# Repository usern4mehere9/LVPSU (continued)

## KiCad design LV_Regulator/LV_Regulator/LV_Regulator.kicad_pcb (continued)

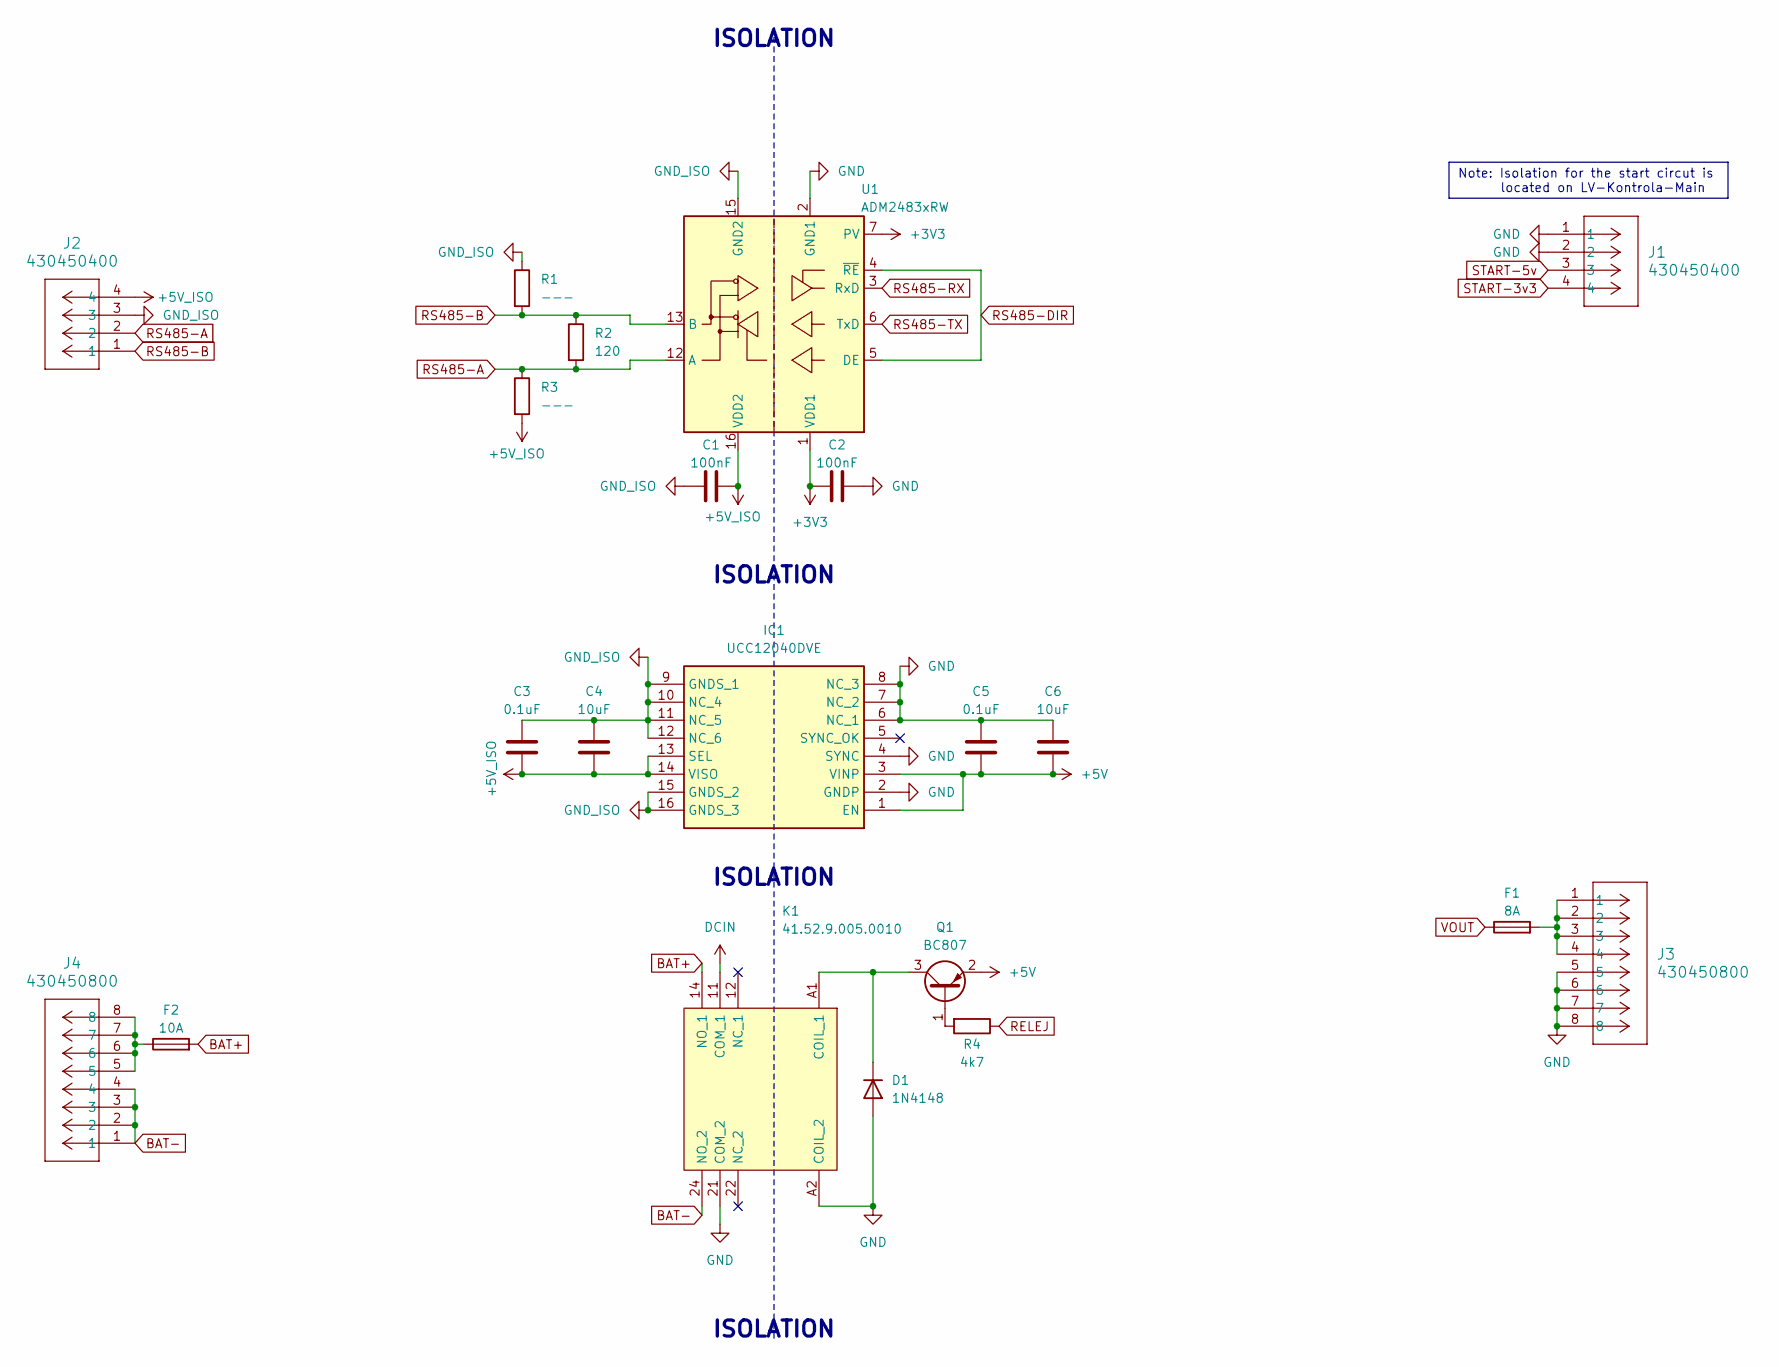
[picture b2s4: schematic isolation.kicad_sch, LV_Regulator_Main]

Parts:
C1, C2: 100nF; C_1206_3216Metric_Pad1.33x1.80mm_HandSolder
C3, C5: 0.1uF; C_1206_3216Metric_Pad1.33x1.80mm_HandSolder
C4, C6: 10uF; C_1206_3216Metric_Pad1.33x1.80mm_HandSolder
D1: 1N4148; D_1206_3216Metric_Pad1.42x1.75mm_HandSolder
F1: 8A; Fuse_1206_3216Metric_Pad1.42x1.75mm_HandSolder
F2: 10A; Fuse_1206_3216Metric_Pad1.42x1.75mm_HandSolder
IC1: UCC12040DVE; SOIC127P1030X265-16N; Mouser Part Number 595-UCC12040DVE
J1, J2: 430450400; CONN_SD-43045-001_04_MOL
J3, J4: 430450800; CONN_SD-43045-001_08_MOL
K1: 41.52.9.005.0010; 415290050010; Manufacturer_Part_Number 41.52.9.005.0010
Q1: BC807; SOT-23W_Handsoldering
R1, R3: ---; R_1206_3216Metric_Pad1.30x1.75mm_HandSolder
R2: 120; R_1206_3216Metric_Pad1.30x1.75mm_HandSolder
R4: 4k7; R_1206_3216Metric_Pad1.30x1.75mm_HandSolder
U1: ADM2483xRW; SOIC-16W_7.5x10.3mm_P1.27mm

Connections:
3V3_EXT: J1.4; also elsewhere on the board
5V_EXT: J1.3; also elsewhere on the board
+5V: C5.1, C6.1, IC1.1 (EN), IC1.3 (VINP), Q1.2 (E); also elsewhere on the board
+5V_ISO: C1.2, C3.1, C4.1, IC1.13 (SEL), IC1.14 (VISO), J2.4, R3.2, U1.16 (VDD2)
BAT+: F2.2, K1.14 (NO_1); also elsewhere on the board
BAT-: J4.1, J4.2, J4.3, J4.4, K1.24 (NO_2); also elsewhere on the board
GND: C2.2, C5.2, C6.2, D1.2 (A), IC1.2 (GNDP), IC1.4 (SYNC), IC1.6 (NC_1), IC1.7 (NC_2), IC1.8 (NC_3), J1.1, J1.2, J3.5, J3.6, J3.7, J3.8, K1.21 (COM_2), K1.A2 (COIL_2), U1.2 (GND1), U1.8 (GND1); also elsewhere on the board
GND_ISO: C1.1, C3.2, C4.2, IC1.9 (GNDS_1), IC1.10 (NC_4), IC1.11 (NC_5), IC1.12 (NC_6), IC1.15 (GNDS_2), IC1.16 (GNDS_3), J2.3, R1.1, U1.9 (GND2), U1.15 (GND2); also elsewhere on the board
unnamed: D1.1 (K), K1.A1 (COIL_1), Q1.3 (C)
unnamed: F1.2, J3.1, J3.2, J3.3, J3.4
unnamed: F2.1, J4.5, J4.6, J4.7, J4.8
unnamed: Q1.1 (B), R4.2
RELEJ: R4.1; also elsewhere on the board
RS485-A: J2.2, R2.2, R3.1, U1.12 (A)
RS485-B: J2.1, R1.2, R2.1, U1.13 (B)
RS485-DIR: U1.4 (~RE), U1.5 (DE); also elsewhere on the board
RS485-RX: U1.3 (RxD); also elsewhere on the board
RS485-TX: U1.6 (TxD); also elsewhere on the board
SYS: K1.11 (COM_1); also elsewhere on the board
VBAT: C2.1, U1.1 (VDD1), U1.7 (PV); also elsewhere on the board
VOUT: F1.1; also elsewhere on the board

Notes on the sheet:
ISOLATION
Note: Isolation for the start circut is located on LV-Kontrola-Main

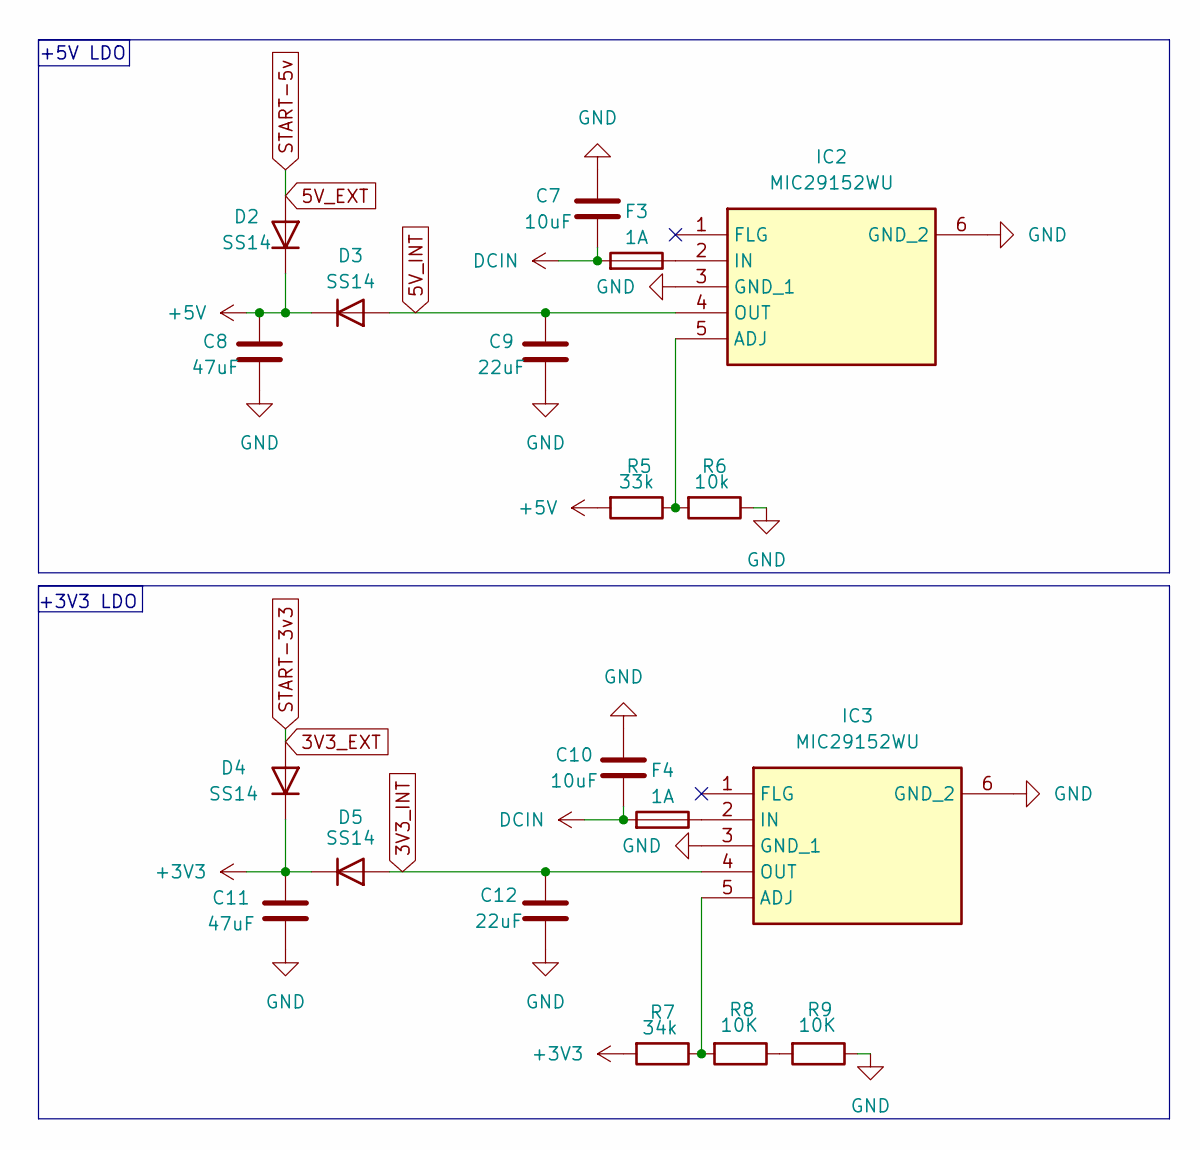
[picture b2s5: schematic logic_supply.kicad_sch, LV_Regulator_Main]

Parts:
C7, C10: 10uF; C_1206_3216Metric_Pad1.33x1.80mm_HandSolder
C8, C11: 47uF; C_1206_3216Metric_Pad1.33x1.80mm_HandSolder
C9, C12: 22uF; C_1206_3216Metric_Pad1.33x1.80mm_HandSolder
D2, D3, D4, D5: SS14; CR_SMA_403AE_OSI
F3, F4: 1A; Fuse_1206_3216Metric_Pad1.42x1.75mm_HandSolder
IC2, IC3: MIC29152WU; Mouser Part Number 998-MIC29152WU
R5: 33k; R_1206_3216Metric_Pad1.30x1.75mm_HandSolder
R6: 10k; R_1206_3216Metric_Pad1.30x1.75mm_HandSolder
R7: 34k; R_1206_3216Metric_Pad1.30x1.75mm_HandSolder
R8, R9: 10K; R_1206_3216Metric_Pad1.30x1.75mm_HandSolder

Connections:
3V3_EXT: D4.2 (A); also elsewhere on the board
3V3_INT: C12.2, D5.2 (A), IC3.4 (OUT); also elsewhere on the board
5V_EXT: D2.2 (A); also elsewhere on the board
5V_INT: C9.2, D3.2 (A), IC2.4 (OUT); also elsewhere on the board
+5V: C8.2, D2.1 (K), D3.1 (K), R5.2; also elsewhere on the board
GND: C7.1, C8.1, C9.1, C10.1, C11.1, C12.1, IC2.3 (GND_1), IC2.6 (GND_2), IC3.3 (GND_1), IC3.6 (GND_2), R6.1, R9.1; also elsewhere on the board
unnamed: IC2.5 (ADJ), R5.1, R6.2
unnamed: F3.1, IC2.2 (IN)
unnamed: IC3.5 (ADJ), R7.1, R8.2
unnamed: F4.1, IC3.2 (IN)
unnamed: R8.1, R9.2
SYS: C7.2, C10.2, F3.2, F4.2; also elsewhere on the board
VBAT: C11.2, D4.1 (K), D5.1 (K), R7.2; also elsewhere on the board

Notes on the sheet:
+5V LDO
+3V3 LDO

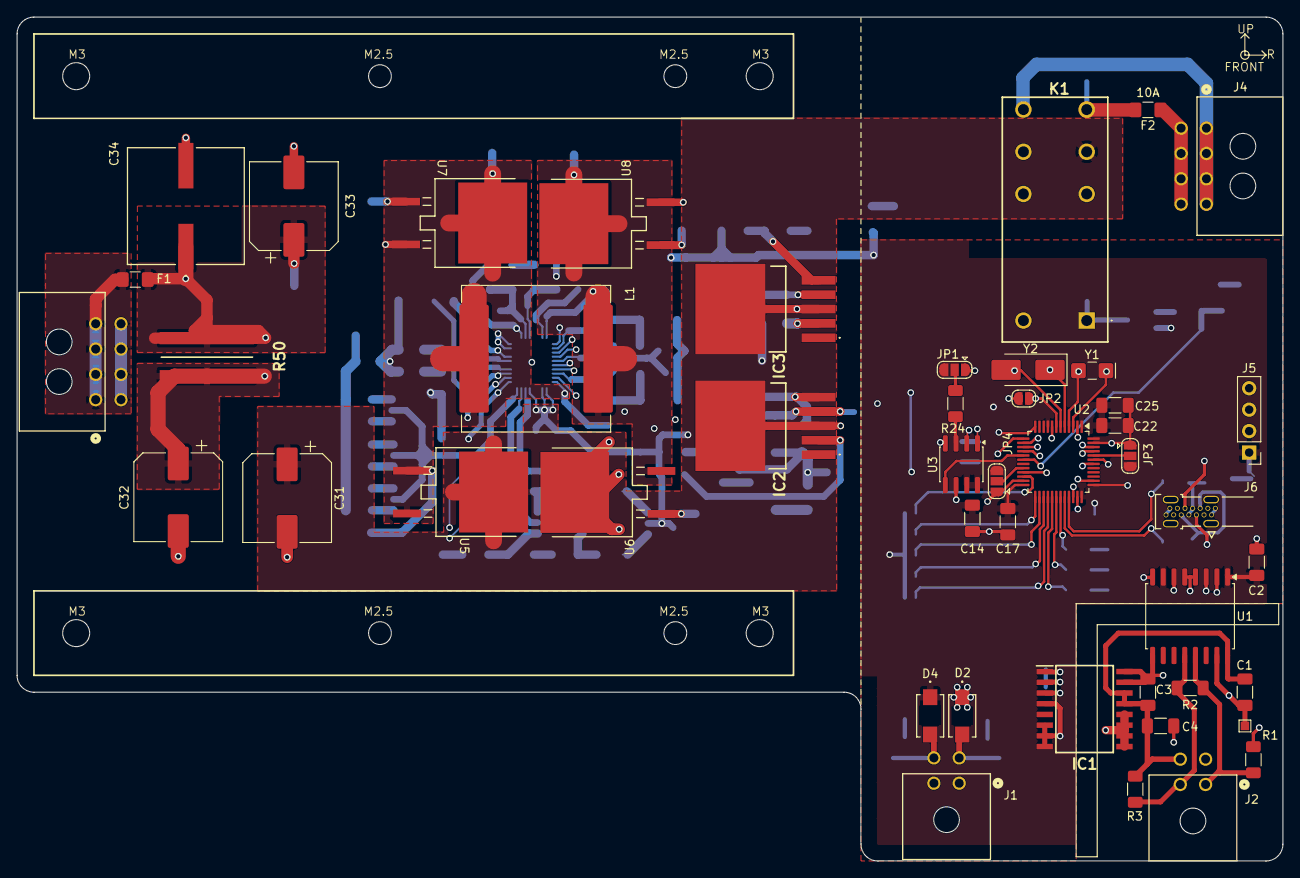
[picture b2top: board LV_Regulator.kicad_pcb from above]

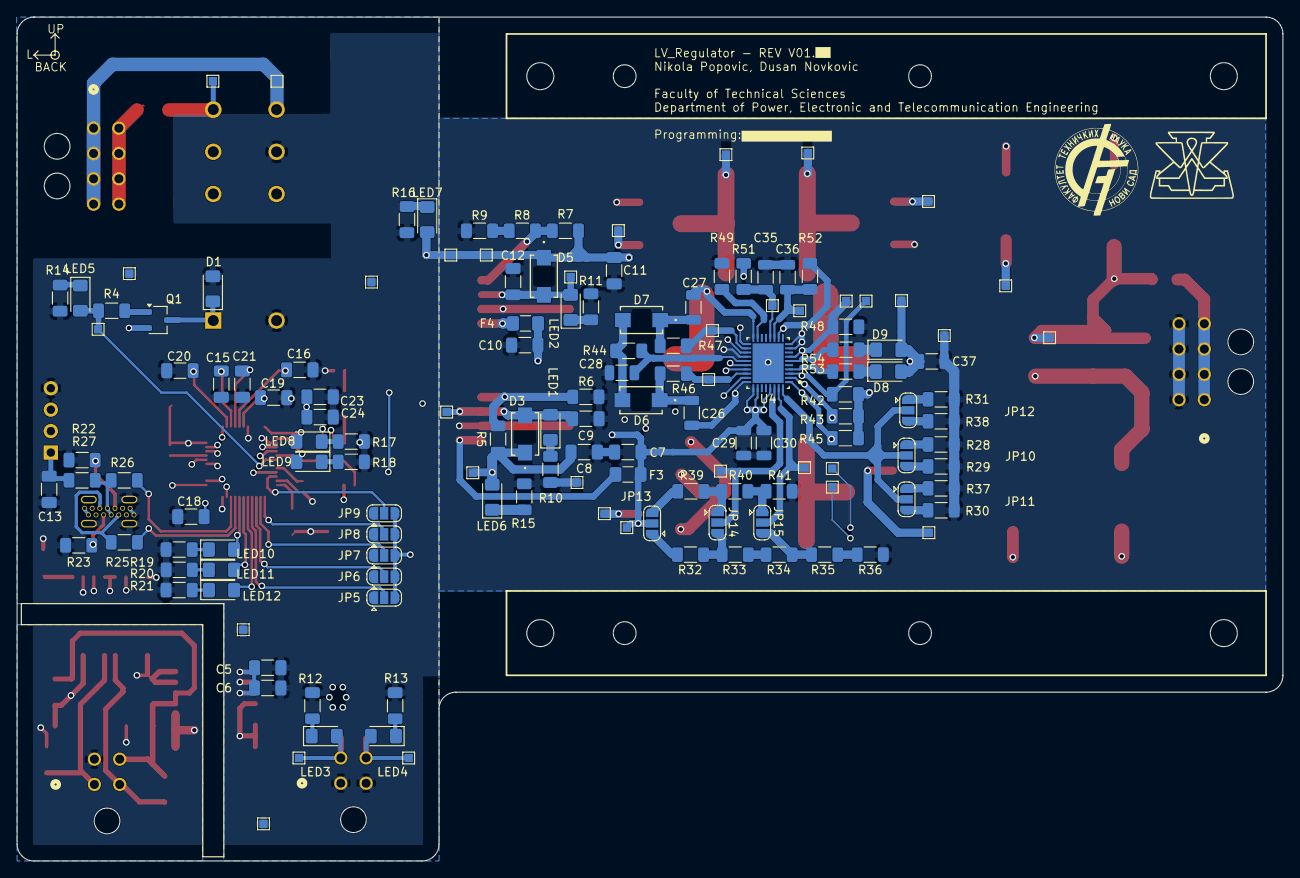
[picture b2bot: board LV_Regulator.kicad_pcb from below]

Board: 4 copper layers, 150.0 x 100.0 mm, 190 parts (144 on the bottom side), 113 nets.

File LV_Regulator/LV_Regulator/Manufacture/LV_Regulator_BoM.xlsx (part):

Id | Designator | Footprint | Quantity | Designation | Supplier and ref
1 | 3V3 | LED_1206_3216Metric_Pad1.42x1.75mm_HandSolder | 1 | 3V3 (YELLOW) | https://www.digikey.com/en/products/detail/kingbright/APT321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 | https://eu.mouser.com/ProductDetail/Bivar/SM1206UYC?qs=jaLxT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
2 | 3V3_EXT | LED_1206_3216Metric_Pad1.42x1.75mm_HandSolder | 1 | 3V3_EXT (YELLOW) | https://www.digikey.com/en/products/detail/kingbright/APT321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 | https://eu.mouser.com/ProductDetail/Bivar/SM1206UYC?qs=jaLxT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
3 | 3V3_INT | LED_1206_3216Metric_Pad1.42x1.75mm_HandSolder | 1 | 3V3_INT (YELLOW) | https://www.digikey.com/en/products/detail/kingbright/APT321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 | https://eu.mouser.com/ProductDetail/Bivar/SM1206UYC?qs=jaLxT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
4 | 5V | LED_1206_3216Metric_Pad1.42x1.75mm_HandSolder | 1 | 5V (RED) | https://www.digikey.com/en/products/detail/kingbright/APT321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 | https://eu.mouser.com/ProductDetail/Bivar/SM1206URC?qs=jaLxT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
5 | 5V_EXT | LED_1206_3216Metric_Pad1.42x1.75mm_HandSolder | 1 | 5V_EXT (RED) | https://www.digikey.com/en/products/detail/kingbright/APT321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 | https://eu.mouser.com/ProductDetail/Bivar/SM1206URC?qs=jaLxT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
6 | 5V_INT | LED_1206_3216Metric_Pad1.42x1.75mm_HandSolder | 1 | 5V_INT (RED) | https://www.digikey.com/en/products/detail/kingbright/APT321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 | https://eu.mouser.com/ProductDetail/Bivar/SM1206URC?qs=jaLxT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
7 | C1, C2, C13, C14, C17, C18, C22, C24, C25 | C_1206_3216Metric_Pad1.33x1.80mm_HandSolder | 9 | 100nF | https://www.digikey.com/en/products/detail/kemet/c1206y104k9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 | https://eu.mouser.com/ProductDetail/KEMET/C1206Y104K9RACTU?q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
8 | C3, C5, C19 | C_1206_3216Metric_Pad1.33x1.80mm_HandSolder | 3 | 0.1uF | https://www.digikey.com/en/products/detail/kemet/c1206y104k9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 | https://eu.mouser.com/ProductDetail/KEMET/C1206Y104K9RACTU?q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
9 | C4, C6, C7, C10, C23 | C_1206_3216Metric_Pad1.33x1.80mm_HandSolder | 5 | 10uF | https://www.digikey.com/en/products/detail/samsung-electro-m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 | https://eu.mouser.com/ProductDetail/Samsung-Electro-Mechanic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
10 | C8, C11 | C_1206_3216Metric_Pad1.33x1.80mm_HandSolder | 2 | 47uF | https://www.digikey.com/en/products/detail/taiyo-yuden/MLASJ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 | https://eu.mouser.com/ProductDetail/TAIYO-YUDEN/MLASJ319LB54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
11 | C9, C12 | C_1206_3216Metric_Pad1.33x1.80mm_HandSolder | 2 | 22uF | https://www.digikey.com/en/products/detail/murata-electronic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 | https://eu.mouser.com/ProductDetail/Murata-Electronics/GGM31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
12 | C15, C20 | C_1206_3216Metric_Pad1.33x1.80mm_HandSolder | 2 | 8pF | https://www.digikey.com/en/products/detail/walsin-technology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 | https://eu.mouser.com/ProductDetail/Walsin/1206N8R0B500CT?qs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
13 | C16, C21 | C_1206_3216Metric_Pad1.33x1.80mm_HandSolder | 2 | 12pF | https://www.digikey.com/en/products/detail/kyocera-avx/KGM31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 | https://eu.mouser.com/ProductDetail/KYOCERA-AVX/12065A120KAT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
14 | C26, C27, C35, C36 | C_1206_3216Metric | 4 | 100nF | https://www.digikey.com/en/products/detail/kemet/c1206y104k9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 | https://eu.mouser.com/ProductDetail/KEMET/C1206Y104K9RACTU?q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
15 | C28, C37 | C_1206_3216Metric | 2 | 4.7uF | https://www.digikey.com/en/products/detail/walsin-technology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 | https://eu.mouser.com/ProductDetail/Walsin/SH31B475K250CT?qs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
16 | C29, C30 | C_1206_3216Metric | 2 | 1uF | https://www.digikey.com/en/products/detail/kemet/c1206c105k1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 | https://eu.mouser.com/ProductDetail/KEMET/C1206C105K1RAC7210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
17 | C31 | CAP_UCD_12P5X13P5_NCH | 1 | 56uF | https://www.digikey.com/en/products/detail/eaton-electronics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 | https://eu.mouser.com/ProductDetail/Eaton-Electronics/EHBSA0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
18 | C32, C33 | CP_Elec_10x10 | 2 | 47uF | https://www.digikey.com/en/products/detail/vishay-beyschlag-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 | https://eu.mouser.com/ProductDetail/Vishay-BC-Components/MAL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
19 | C34 | CAP_UCD_12P5X13P5_NCH | 1 | 180uF | https://www.digikey.com/en/products/detail/nichicon/ucz1j181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 | https://eu.mouser.com/ProductDetail/Nichicon/UCZ1J181MNS1MS?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
20 | COM, START | CONN_SD-43045-001_04_MOL | 2 | 430450400 | https://www.digikey.com/en/products/detail/molex/0430450400/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 | https://eu.mouser.com/ProductDetail/Molex/43045-0400?qs=UeCe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
21 | D1 | D_1206_3216Metric_Pad1.42x1.75mm_HandSolder | 1 | 1N4148 | https://www.digikey.com/en/products/detail/taiwan-semiconduc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 | https://eu.mouser.com/ProductDetail/Taiwan-Semiconductor/1N4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
22 | D2, D3, D4, D5, D6, D7 | CR_SMA_403AE_OSI | 6 | SS14 | https://www.digikey.com/en/products/detail/onsemi/SS14/965474 | https://eu.mouser.com/ProductDetail/onsemi/SS14?qs=mVVXn4M53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
23 | D8, D9 | D_1206_3216Metric_Pad1.42x1.75mm_HandSolder | 2 | LED(YELLOW) | https://www.digikey.com/en/products/detail/kingbright/APT321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 | https://eu.mouser.com/ProductDetail/Bivar/SM1206UYC?qs=jaLxT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
24 | DIAG | MOLEX_2169890001 | 1 | 2169890001 | https://www.digikey.com/en/products/detail/wec/216989-0001/29353332 | https://eu.mouser.com/ProductDetail/Molex/216989-0001?qs=DRk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
25 | ERR | LED_1206_3216Metric_Pad1.42x1.75mm_HandSolder | 1 | ERR(RED) | https://www.digikey.com/en/products/detail/kingbright/APT321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 | https://eu.mouser.com/ProductDetail/Bivar/SM1206URC?qs=jaLxT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
26 | F1 | Fuse_1206_3216Metric_Pad1.42x1.75mm_HandSolder | 1 | 8A | https://www.digikey.com/en/products/detail/bel-fuse-inc/C1F-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 | https://eu.mouser.com/ProductDetail/Bel-Fuse/C1F-8?qs=Mr%252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
27 | F2 | Fuse_1206_3216Metric_Pad1.42x1.75mm_HandSolder | 1 | 10A | https://www.digikey.com/en/products/detail/bel-fuse-inc/0685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 | https://eu.mouser.com/ProductDetail/Bel-Fuse/0685P9100-01?qs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
28 | F3, F4 | Fuse_1206_3216Metric_Pad1.42x1.75mm_HandSolder | 2 | 1A | https://www.digikey.com/en/products/detail/bel-fuse-inc/C1F-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 | https://eu.mouser.com/ProductDetail/Bel-Fuse/C1F-1?qs=Mr%252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
29 | IC1 | SOIC127P1030X265-16N | 1 | UCC12040DVE | https://www.digikey.com/en/products/detail/texas-instruments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 | https://eu.mouser.com/ProductDetail/Texas-Instruments/UCC120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
30 | IC2, IC3 | MIC29152WU | 2 | MIC29152WU | https://www.digikey.com/en/products/detail/microchip-technol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 | https://eu.mouser.com/ProductDetail/Microchip-Technology/MIC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
31 | J3, PWR_IN | CONN_SD-43045-001_08_MOL | 2 | 430450800 | https://www.digikey.com/en/products/detail/molex/0430450800/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 | https://eu.mouser.com/ProductDetail/Molex/43045-0800?qs=MGlP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
32 | K1 | LED_1206_3216Metric_Pad1.42x1.75mm_HandSolder | 1 | REL(GREEN) | https://www.digikey.com/en/products/detail/kingbright/APT321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 | https://eu.mouser.com/ProductDetail/Bivar/SM1206GC?qs=jaLxTF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
33 | K1 | 415000000000 | 1 | 41.52.9.005.0010 | https://elektroleum.rs/proizvod/finder-41-52-9-005-0010-pcb-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 | //
34 | L1 | L_APV_APH1770 | 1 | 10uH | https://www.digikey.com/en/products/detail/bourns-inc/srp177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 | https://eu.mouser.com/ProductDetail/Bourns/SRP1770TA-100M?qs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
35 | OK | LED_1206_3216Metric_Pad1.42x1.75mm_HandSolder | 1 | OK (GREEN) | https://www.digikey.com/en/products/detail/kingbright/APT321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 | https://eu.mouser.com/ProductDetail/Bivar/SM1206GC?qs=jaLxTF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
36 | Q1 | SOT-23W_Handsoldering | 1 | BC807 | https://www.digikey.com/en/products/detail/onsemi/BC807-25LT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 | https://eu.mouser.com/ProductDetail/Rectron/BC807?qs=7pEAo90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
37 | R1, R3, R42, R43, R44, R45, R46, R47, R48 | R_1206_3216Metric_Pad1.30x1.75mm_HandSolder | 9 | --- | https://www.digikey.com/en/products/detail/yageo/rc1206jr-07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 | https://eu.mouser.com/ProductDetail/YAGEO/RC1206JR-070RL?qs=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
38 | R2 | R_1206_3216Metric_Pad1.30x1.75mm_HandSolder | 1 | 120 | https://www.digikey.com/en/products/detail/yageo/ar1206jr-07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 | https://eu.mouser.com/ProductDetail/YAGEO/RC1206JR-070RL?qs=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
39 | R4 | R_1206_3216Metric_Pad1.30x1.75mm_HandSolder | 1 | 4k7 | https://www.digikey.com/en/products/detail/yageo/re1206dre07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 | https://eu.mouser.com/ProductDetail/YAGEO/RE1206DRE074K7L?qs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
40 | R5 | R_1206_3216Metric_Pad1.30x1.75mm_HandSolder | 1 | 33k | https://www.digikey.com/en/products/detail/yageo/rt1206brd07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 | https://eu.mouser.com/ProductDetail/YAGEO/RT1206BRD0733KL?qs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
41 | R6, R53, R54 | R_1206_3216Metric_Pad1.30x1.75mm_HandSolder | 3 | 10k | https://www.digikey.com/en/products/detail/rohm-semiconducto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 | https://eu.mouser.com/ProductDetail/ROHM-Semiconductor/SFR18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

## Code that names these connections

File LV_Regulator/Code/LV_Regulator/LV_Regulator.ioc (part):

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Mcu.Name=STM32F103C(8-B)Tx
Mcu.Package=LQFP48
Mcu.UserName=STM32F103C8Tx
PA0-WKUP.Signal=ADCx_IN0
PA1.Signal=ADCx_IN1
PA10.GPIOParameters=GPIO_Label
PA10.GPIO_Label=DIAG_RX
PA10.Signal=GPIO_Output
PA11.Mode=Device
PA11.Signal=USB_DM
PA12.Mode=Device
PA12.Signal=USB_DP
PA13.Mode=Serial_Wire
PA13.Signal=SYS_JTMS-SWDIO
PA14.Mode=Serial_Wire
PA14.Signal=SYS_JTCK-SWCLK
PA15.GPIOParameters=GPIO_Label
PA15.GPIO_Label=CE_N
PA15.Signal=GPIO_Output
PA2.GPIOParameters=GPIO_Label
PA2.GPIO_Label=DIAG_OK
PA2.Signal=GPIO_Output
PA3.GPIOParameters=GPIO_Label
PA3.GPIO_Label=DIAG_ERR
PA3.Signal=GPIO_Output
PA4.Mode=NSS_Signal_Hard_Output
PA4.Signal=SPI1_NSS
PA5.Mode=Full_Duplex_Master
PA5.Signal=SPI1_SCK
PA6.Mode=Full_Duplex_Master
PA6.Signal=SPI1_MISO
PA7.Mode=Full_Duplex_Master
PA7.Signal=SPI1_MOSI
PA8.GPIOParameters=GPIO_Label
PA8.GPIO_Label=DIAG_RUN
PA8.Signal=GPIO_Output
PA9.GPIOParameters=GPIO_Label
PA9.GPIO_Label=DIAG_TX
PA9.Signal=GPIO_Output
PB0.GPIOParameters=GPIO_Label
PB0.GPIO_Label=RELEJ
PB0.Signal=GPIO_Output
PB10.GPIOParameters=GPIO_Label
PB10.GPIO_Label=INT_N
PB10.Signal=GPIO_Input
PB11.GPIOParameters=GPIO_Label
PB11.GPIO_Label=ADR1
PB11.Signal=GPIO_Output
PB12.GPIOParameters=GPIO_Label
PB12.GPIO_Label=ADR2
PB12.Signal=GPIO_Output
PB13.GPIOParameters=GPIO_Label
PB13.GPIO_Label=ADR3
PB13.Signal=GPIO_Output
PB14.GPIOParameters=GPIO_Label
PB14.GPIO_Label=ADR4
PB14.Signal=GPIO_Output
PB15.GPIOParameters=GPIO_Label
PB15.GPIO_Label=ADR5
PB15.Signal=GPIO_Output
PB2.GPIOParameters=GPIO_Label
PB2.GPIO_Label=BOOT1
PB2.Signal=GPIO_Input
PB6.Mode=Asynchronous
PB6.Signal=USART1_TX
PB7.Mode=Asynchronous
PB7.Signal=USART1_RX
PB8.Mode=I2C
PB8.Signal=I2C1_SCL
PB9.Mode=I2C
PB9.Signal=I2C1_SDA
PC13-TAMPER-RTC.GPIOParameters=GPIO_Label
PC13-TAMPER-RTC.GPIO_Label=USART1_DIR
PC13-TAMPER-RTC.Signal=GPIO_Output
PC14-OSC32_IN.Mode=LSE-External-Oscillator
PC14-OSC32_IN.Signal=RCC_OSC32_IN
PC15-OSC32_OUT.Mode=LSE-External-Oscillator
PC15-OSC32_OUT.Signal=RCC_OSC32_OUT
PD0-OSC_IN.Mode=HSE-External-Oscillator
PD0-OSC_IN.Signal=RCC_OSC_IN
PD1-OSC_OUT.Mode=HSE-External-Oscillator
PD1-OSC_OUT.Signal=RCC_OSC_OUT
RCC.SYSCLKFreq_VALUE=72000000
RCC.SYSCLKSource=RCC_SYSCLKSOURCE_PLLCLK
board=custom

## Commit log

2026-01-19 Initial commit
    Blank KiCad files for later use
2026-01-19 Folder structure added
    Added a folder structure for documentation, code and component data; Added basic info to KiCad files
2026-01-20 Added components
    Added some basic isolation components to the LV_Regulator schematic.
2026-01-20 Modified LV_Regulator schematic; Added basic code configuration for LV_Reulator
    Added the MCU to the schematic and some basic passives around it;
    Added the basic STM32 program structure and set up the pin configuration to reflect the schematic.
2026-01-26 Created initial STM projects
    Created basic blank project and added some pin definitions
2026-01-31 Added LDOs
    Added the two LDOs for 3v3 and 5v logic supply.
2026-02-03 Kicad Schematic Progress
    Put down basic components and imported TI FET's & Buck-Boost Controller, as well as some of the basic connections between Controller and FET's.
2026-02-03 Added a lot
    Created a schematic hierarchy for LV_Regulator, added connectors, added start logic, added address select jumpers for RS485, implemented start isolation on LV_Kontrola_Main,...
2026-02-03 Kicad Regulator & Buck Boost controller Schematic Progress
    Put down basic components and imported TI FET's & Buck-Boost Controller, as well as some of the basic connections between Controller and FET's.
2026-02-05 Fixed last commit
    Fixed all mistakes from the last push
2026-02-05 Added Start Control
    Added Start Control MCU to the LV_Kontrola_Main, added hsc/lsc to LV_Regulator, fixed component numbering
2026-02-09 Added Stat logic
    Added start mcu and associated components to the LV_Kontrola_Main schematic, added STM32CubeIDE project and basic configuration, added fuses to LV_Regulator
2026-02-10 Continuation of BQ25858 Schematic drawing
    Added more components from the examples schematic provided from TI.
2026-03-03 LV_Regulator Control changes
    Added debug and development equipment, added config. eeprom, more...
2026-03-11 Update & Further Progress on Regulator Controller Schematic
    Nikola Popovic added Frequency choice jumpers
    I added Jumpers for Voltage trigger selection
    Made global Labels for MCU pin connection, connected PG & STAT Diodes as well as connected ACN & ACP pins.
2026-03-11 Update Schematic, moved MOSFETS box
2026-03-11 Updated Note for Regulator
2026-03-12 Regulator Update & MCU pins
    Update schematic and connected Regulator to MCU
2026-03-16 added certain footprints
    Added footprints for certain parts such as the BQ25858Q1 regulator controller & CSD19506 MOSFET for PCB design and put in footprints (will need change)
2026-03-17 Various changes
2026-03-17 Multiple Footprints Added
2026-03-18 Changes of PCB and Schematic files for the LV_Regulator
    Removed old LDOs, added new LDOs, defined initial pcb size and I/O ports
2026-03-20 Update to LV_Regulator schematic
    Chosen some component's footprints as well as made a page for test points, etc.
2026-03-20 Multiple Updates
    Added footprints and purchase links to the MCU page and updated some footprints on the Regulator Page from smd to SMD Handsolder
2026-03-20 Added footprints and Test points
    Added test points, yet to connect them have to find where they all go exactly
2026-03-27 Added Footprints & Links for Component Purchase
2026-03-28 PCB Layout definitions part 2
    Added isolation keepouts
2026-03-28 Halfway Push of adding 3D models to PCB layout components
    Pushing with components left to add to finish on main PC
2026-03-29 Added 3D models to components part 2
    Modeled some Custom .step models for components whose 3D models I couldn't find, and imported the rest.
2026-03-31 Initial Routing for tje LV_Regulator control portion
    Changes to the schematic were made for simpler routing
2026-04-03 LV Regulator Switching layout Started
    Rough placement of components bigger components, a well as giving a capacitor a 3D model it lacked for the 3D View.
    More precise placement is in queue and actual PCB routing.
2026-04-04 Component Placement and Routing
2026-04-07 Continued PCB Routing
2026-04-07 PCB routing and TP placement
    Finished first PCB routing and started TP placement
2026-04-07 Changes to LV_Kontrola_Main
    Added a lot to the schematic, fixed component libs, mics...
2026-04-08 Deleted Draft Regulator and Test Points Routing
    Deleted Draft Routing of the Regulator and Power Electronics side of the board, because layout was not optimal in the slightest, & will replace and re-route the whole power electronics side.
2026-04-08 Multiple Fixes in Schematic & Routing
    Fixed multiple issues in schematic, like adding jumpers to isolate ACUV/ACOV between the choices. Moved the fuses on the Logic_Supply as per instruction of professor from Chair of Electronics, FoTS, 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
2026-04-14 Small corrections to the control part of LV_Regulatoe
    Changes to the PCB.
2026-04-14 PCB Routing
    Did some PCB Routing, added components for 5V Logic regulator, some routing around the BQ25858 IC, will probably need clean up.
2026-04-28 PCB Routing progress
2026-05-14 Major PCB Routing Progress
    Finished routing of all Regulator & Power components and connections.
    Also routed & placed a good amount of power electronics side TP's, only a few left which are Logic Supply TP's and the MCU side TP's.
    Only Routing on the Power side left are the few remaining test points.
    Additional detail, removed all Teardrops because of their deletion residue, in doing so, I've also removed all the residue.
    Tear drops will be added after final routing for the revision has been finished.
2026-05-17 Redesigned the control section of the LV_Regulator
    The routing of the control section was redone completely, LED's were labeled with their function, some signals were renamed for consistency, removed redundant testpoints, removed names of testpoints,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
2026-05-17 Folder structure changes
    The folder structures were changed to comply with current FS Black Hornets GitHub repository templates. Separated out all the elements of the LV_Kontrola subsystem.
2026-05-17 Fixed some readmes
    Fixed some readmes to comply with some parts of the FS Black Hornets repository template. (Parts required for the overall schematic)
2026-05-18 Fixed DRC & some other minor tweaks
2026-05-19 Started BOM work
2026-06-01 PCB changes
    Changes to the silkscreen of the pcb, added mounting holes, modified the schematic to comply with the template, more...
2026-06-01 Finished BoM Sheet, Fixed Component issues.
    Fixed DRC Errors, as well as changing a Capacitor that was not chosen correctly. And have filled Bill of Materials.
2026-06-01 Fixed Capacitor choice
    Mixed up Capacitor choices, fixed the issue
2026-06-02 Finished BoM
2026-06-02 Added graphics to PCB
2026-06-05 Started LV_Kontrola_Start pcb
2026-06-22 Documentation
